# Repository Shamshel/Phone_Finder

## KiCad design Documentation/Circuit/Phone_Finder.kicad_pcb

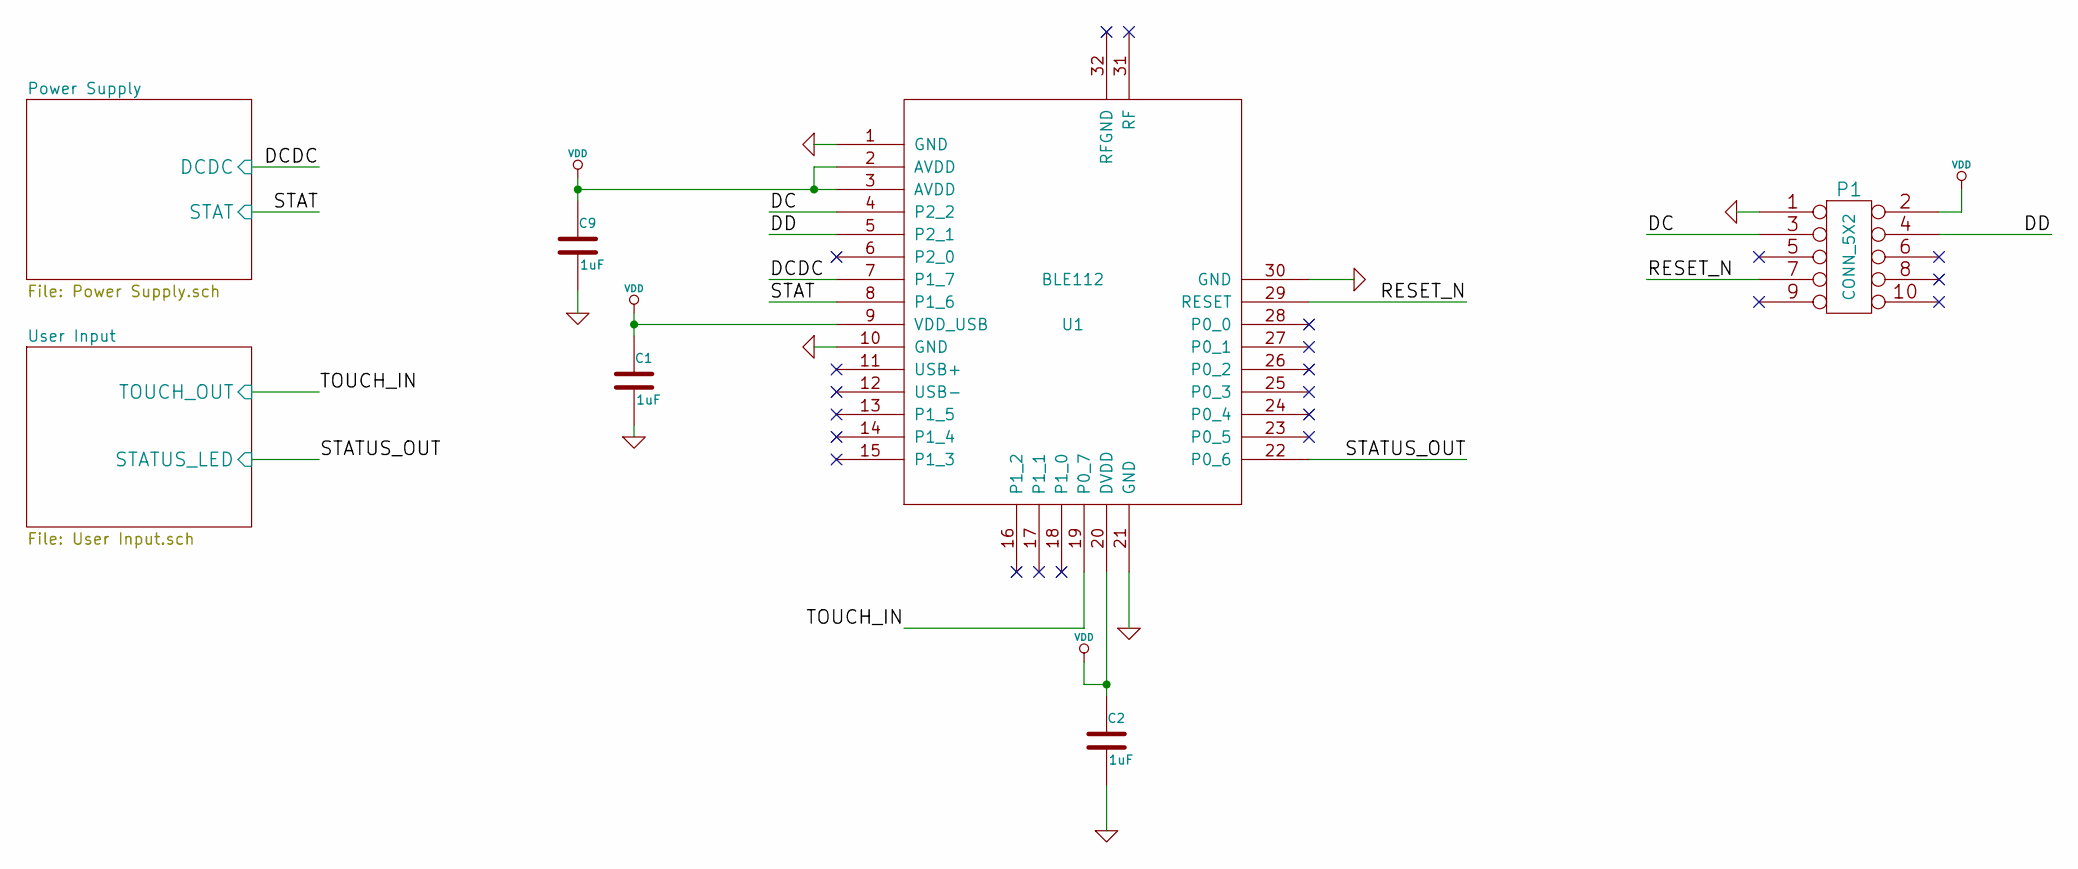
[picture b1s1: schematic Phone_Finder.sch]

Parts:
C1, C2, C9: 1uF
P1: CONN_5X2
U1: BLE112; MODULE

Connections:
/DC: P1.3, U1.4 (P2_2)
/DD: P1.4, U1.5 (P2_1)
/Power Supply/DCDC: U1.7 (P1_7); also elsewhere on the board
/Power Supply/STAT: U1.8 (P1_6); also elsewhere on the board
/RESET_N: P1.7, U1.29 (RESET)
/User Input/STATUS_LED: U1.22 (P0_6); also elsewhere on the board
/User Input/TOUCH_OUT: U1.19 (P0_7); also elsewhere on the board
GND: C1.2, C2.2, C9.2, P1.1, U1.1 (GND), U1.10 (GND), U1.21 (GND), U1.30 (GND); also elsewhere on the board
VDD: C1.1, C2.1, C9.1, P1.2, U1.2 (AVDD), U1.3 (AVDD), U1.9 (VDD_USB), U1.20 (DVDD); also elsewhere on the board

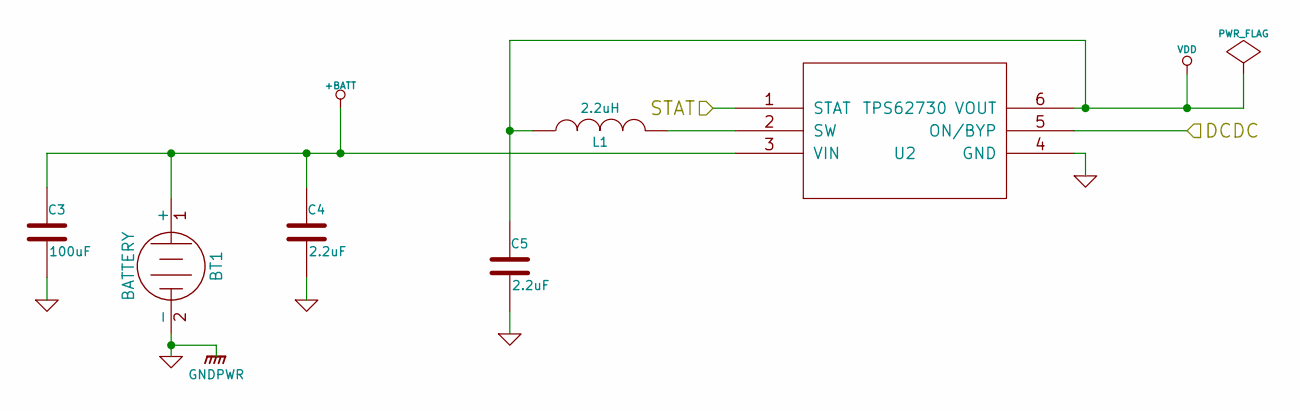
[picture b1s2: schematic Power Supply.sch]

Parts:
BT1: BATTERY
C3: 100uF
C4, C5: 2.2uF
L1: 2.2uH
U2: TPS62730; MODULE

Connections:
+BATT: BT1.1 (+), C3.1, C4.1, U2.3 (VIN)
/Power Supply/DCDC: U2.5 (ON/BYP); also elsewhere on the board
/Power Supply/STAT: U2.1 (STAT); also elsewhere on the board
GND: BT1.2 (-), C3.2, C4.2, C5.2, U2.4 (GND); also elsewhere on the board
unnamed: L1.2, U2.2 (SW)
VDD: C5.1, L1.1, U2.6 (VOUT); also elsewhere on the board

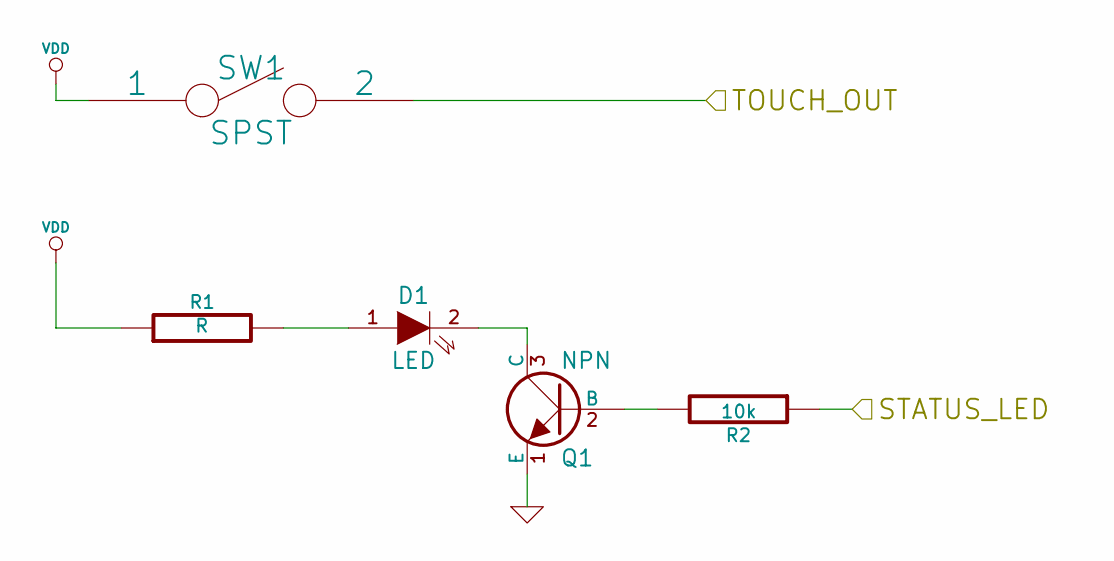
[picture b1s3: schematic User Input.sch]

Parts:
D1: LED
Q1: NPN
R1: R
R2: 10k
SW1: SPST

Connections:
/User Input/STATUS_LED: R2.1; also elsewhere on the board
/User Input/TOUCH_OUT: SW1.2; also elsewhere on the board
GND: Q1.1 (E); also elsewhere on the board
unnamed: D1.1 (A), R1.2
unnamed: D1.2 (K), Q1.3 (C)
unnamed: Q1.2 (B), R2.2
VDD: R1.1, SW1.1; also elsewhere on the board

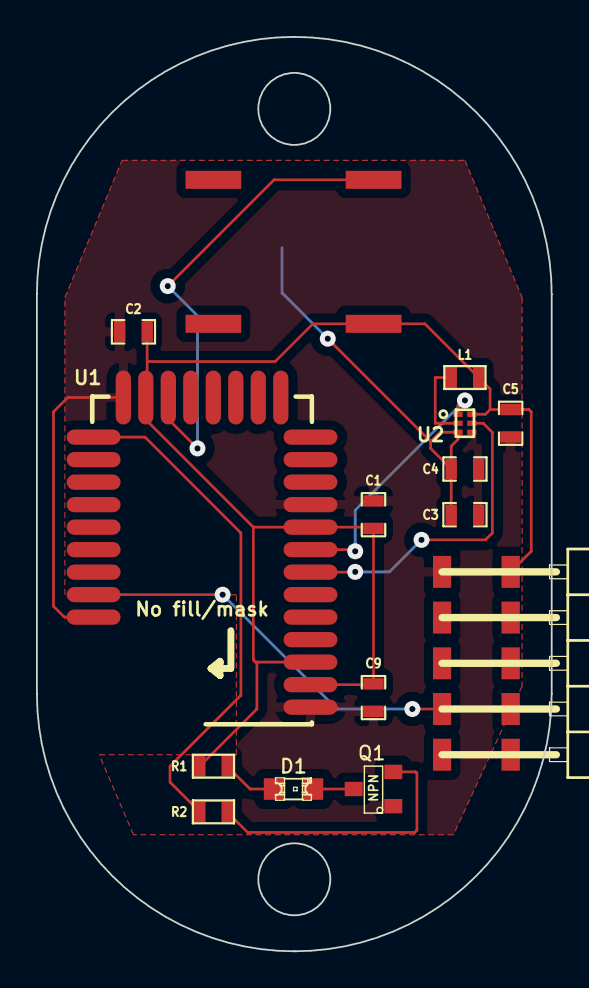
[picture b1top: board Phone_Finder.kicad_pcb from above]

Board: 2 copper layers, 28.6 x 50.8 mm, 16 parts (1 on the bottom side), 14 nets.

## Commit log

2015-05-25 :tada: Added .gitattributes & .gitignore files
2015-05-26 Added Customer Requirements
    Added and fleshed out Customer Requirements document, Engineering
    Requirements document pending approval of Customer Requirements.
2015-05-28 Chipset and Power Investigation
    Investigated and took notes for various chipsets for a BLE/Bluetooth
    Smart implementation.
2015-05-29 Added datasheets and worked on requirements
    Added datasheets for promising IC's, worked on adding specific
    engineering requirements and updating/improving customer requirements.
2015-06-01 Added documents, Engineering Requirements
    Added datasheets and whitepapers for prospective parts and methods.
    Added images for "dog tag" necklace dimensions. The official document
    for these dimensions is A-A-55245, but no (free) download has yet been
    found. Worked on Engineering Requirements. Engineering Requirements
    still needs work in Testing and Verification section.
2015-06-01 Found ID tag specification document
    Found the DoD specification document for personnel dog tags. Document
    ID was actually A-A-55305.
2015-06-01 Added datasheets
    Found coin cell battery holder with retaining clip for shock and
    vibration absorption. Added datasheet for BLE112, the BLE113 is a class
    3 device and is underpowered for the application specifications.
2015-06-02 Added schematic, BLE112 Datasheet
    Began work on the system schematic. System schematic currently assumes
    primary (non-rechargeable) coin-cell battery operating at a nominal 3V.
    Step-down buck converter circuit follows recommended schematic from the
    BLE112 datasheet (pg 19).
2015-06-04 Worked on schematic and PCB
    Worked on circuit schematic. Circuits utilized should reflect those in
    the BLE112 and AT42 datasheets. Added initial PCB layout. Routing
    still needs to be done for PCB layout. Circuit layout should be double
    checked before routing. Refer to an-kd02_103 for more details on touch
    interface layout. Refer to tps62732 datasheet for more details on power
    system layout.
2015-06-09 Modified input circuitry, remade PCB
    Changed input circuit from Atmel's QTouch chipset to a simple momentary
    pushbutton, added datasheet for said pushbutton. Button is dust tight
    and waterproof as per spec doc.
    Changed passives to use 0603 footprint instead of 0402 to provide easier
    reflowing.
    Performed initial layout, connectivity, and ground pours.
2015-06-11 Added BoM, OSHpark estimate
    Added BoM, added estimated cost for board fabrication from OSHpark.
